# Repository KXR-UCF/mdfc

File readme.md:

## **LTI Modular DAQ & Flight Computer**

This is a teensy 4.1 based analog data acquisition system and flight computer.

It consists of 5 PCBs:

**Heisenberg (Mainboard)**

The Heisenberg board carries the Teensy 4.1 and all the modules, mounts to the chassis, and has the servo/aux connector. It provides the same pinout to each of the two modules so they are interchangeable.

**Fring/Schrader (Flight/Ground Power Modules, these will most likely be two different PCBs)**

These boards convert input voltage, either from battery during flight use or power over ethernet for ground use, into the necessary voltages for the rest of the system. They also handle the ethernet input to the Teensy 4.1, and allow the Teensy 4.1 to independently enable/disable each voltage output.

**Goodman (ADC Module)**
This board carries the HiLetgo ADS1256 board, along with analog circuitry and a sensor connector, for use with analog sensors such as Pressure Transducers, Thermocouples, and Load Cells. A future development will be to create a fully SRAD ADC module instead of relying on the COTS ADS1256 board.

**Pinkman (Flight Sensor/Telemetry Module)**
This board contains flight sensors (IMU and barometric), a GPS receiver, and a 433 MHz LoRa radio for telemetry in flight.

The Heisenberg board has 2 module slots and 1 power module slot, and its two primary configurations are as follows:

* DAQ/Ground use: 
	Module A: Goodman
	Module B: Goodman
	Power Module: Schrader
PoE powered, 16 channel analog input, no flight sensor/telemetry, no servo output.
* Flight use:
	Module A: Goodman
	Module B: Pinkman
	Power Module: Fring
Battery powered, 8 channel analog input, flight sensors/telemetry, servo output.

**The primary goals of this project are:**

* Emulate the EE design, collaboration, integration, and test processes used in the aerospace industry to provide a valuable learning experience for members
* Increase the sampling speed of the DAQ system
* Increase the expandability of the DAQ system
* Move ADCs closer to sensors to decrease analog wire length for less noise
* Improve power filtering for ADCs and load cells
* Record fast analog data in flight
* Transmit flight data to ground via telemetry at the highest speed possible
* Create a platform that can be expanded and upgraded by future students

## Copyright

Copyright © 2026 Knights Experimental Rocketry (KXR). All Rights Reserved.

No permission is granted to reproduce, modify, distribute, manufacture from,
or commercially use the contents of this repository without written
authorization from KXR.

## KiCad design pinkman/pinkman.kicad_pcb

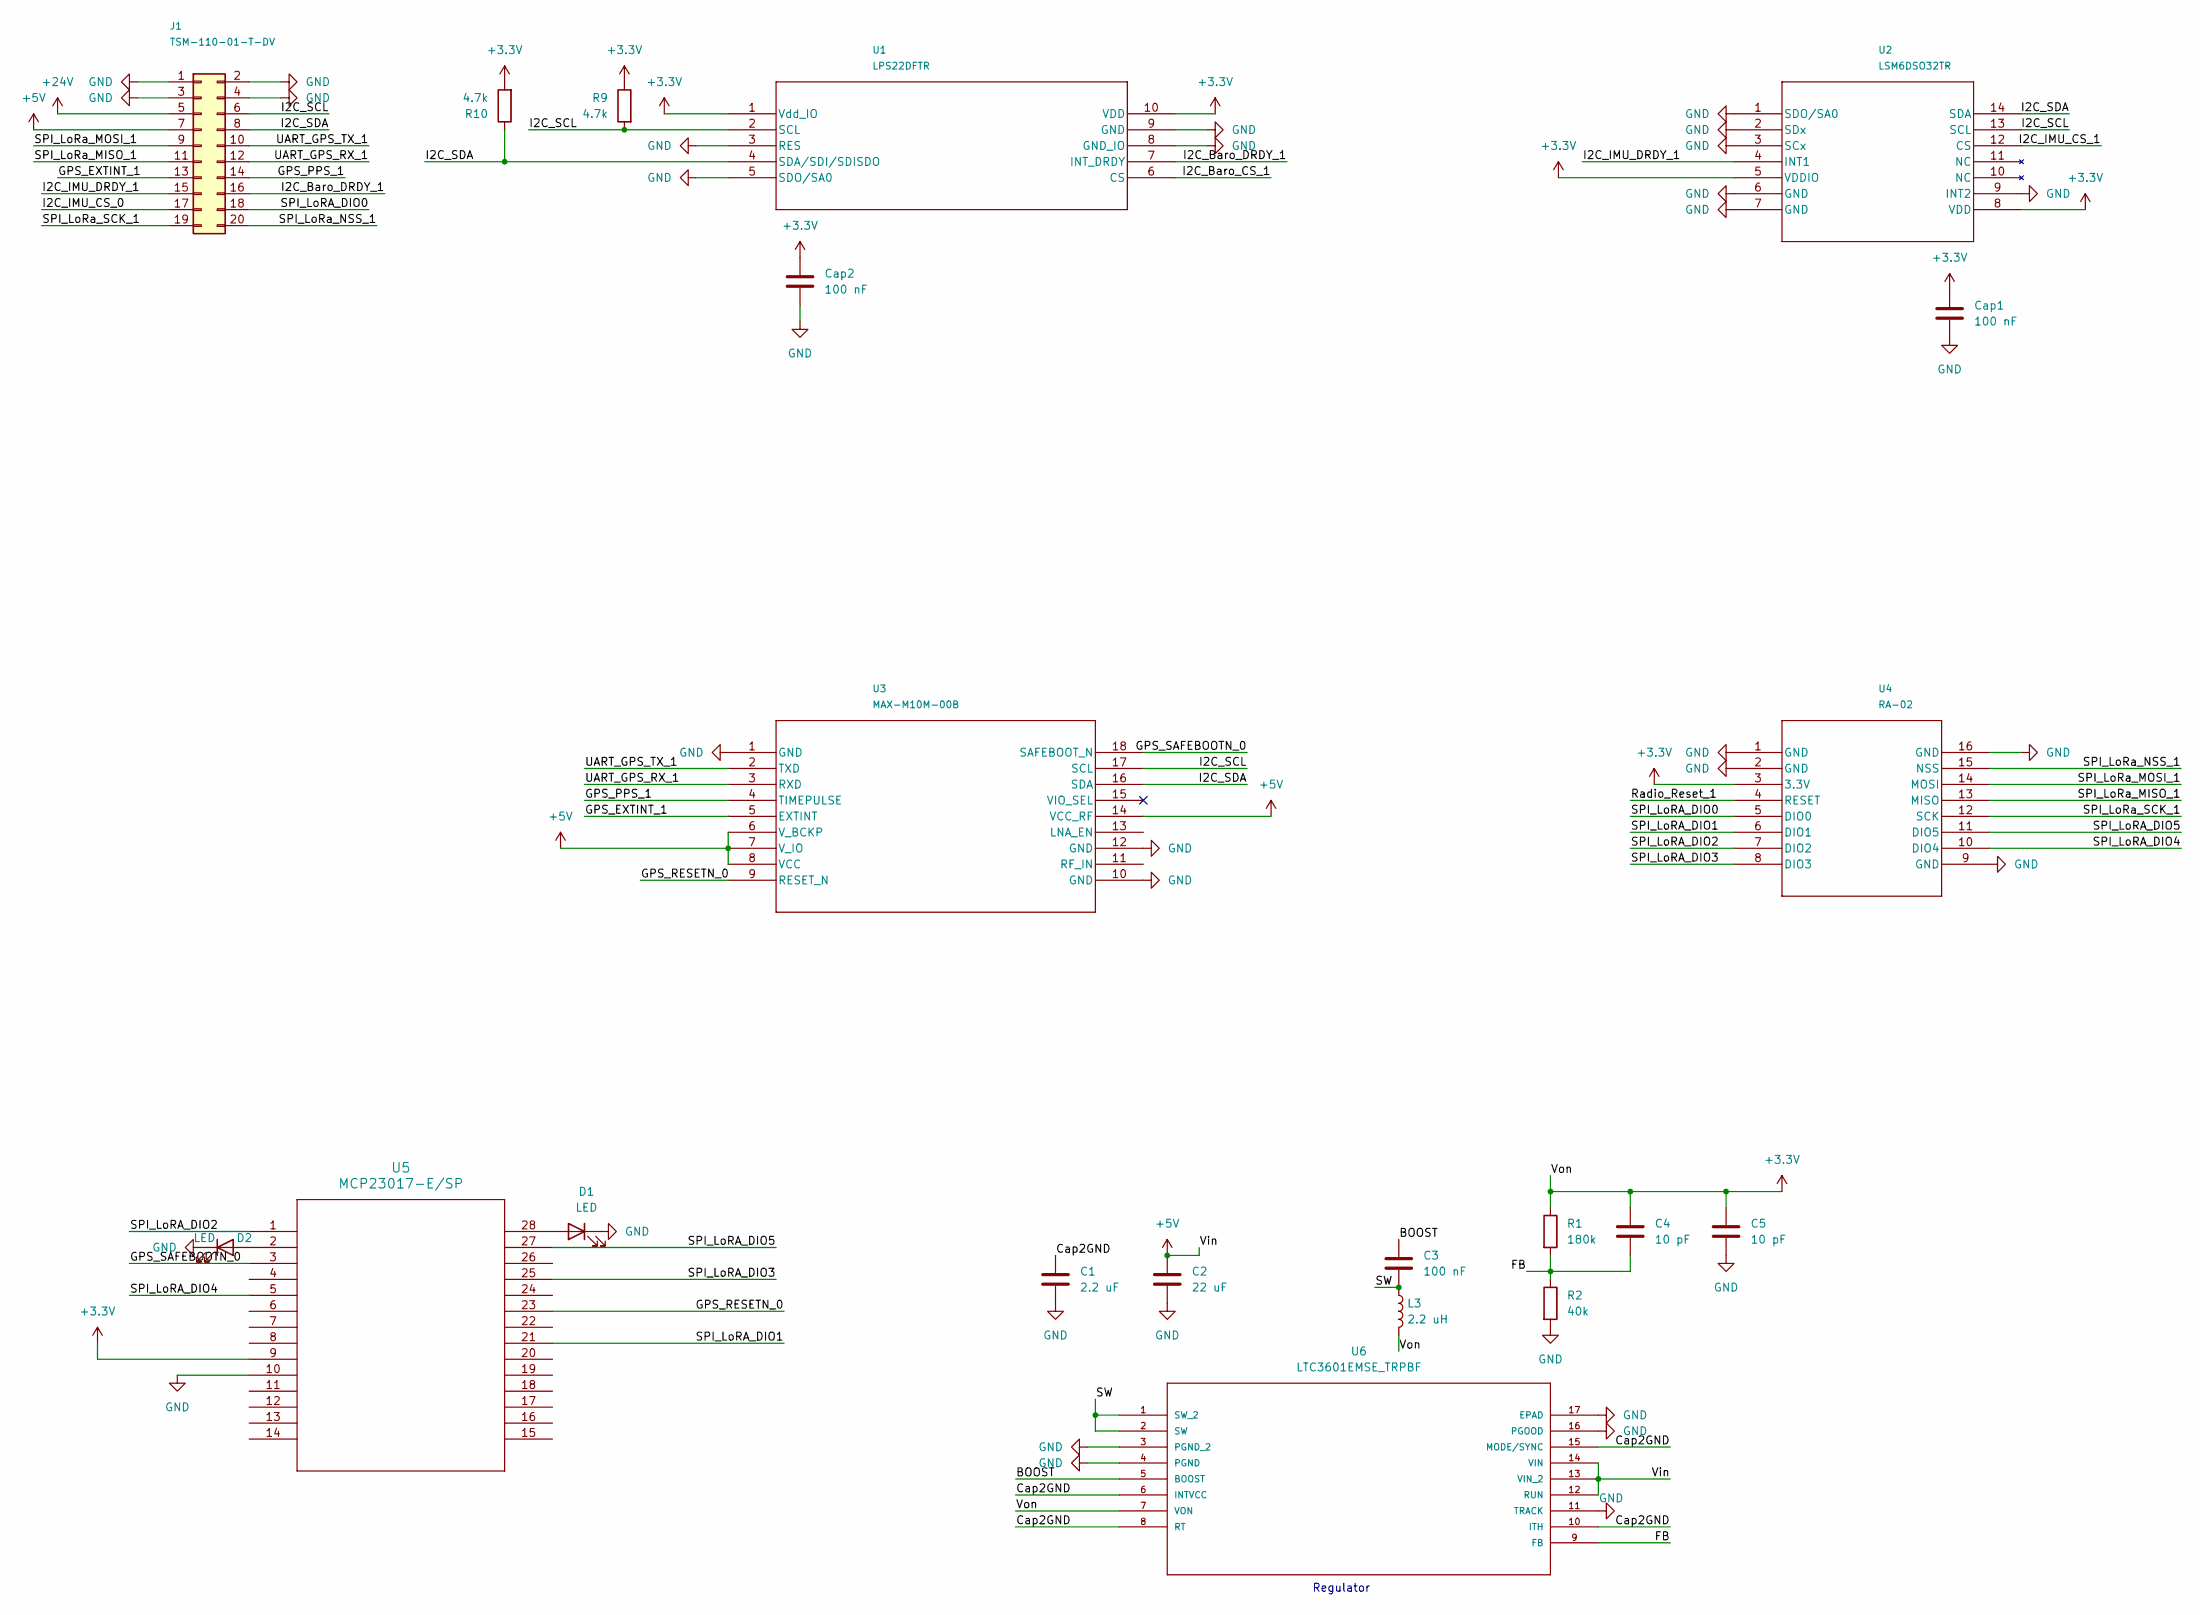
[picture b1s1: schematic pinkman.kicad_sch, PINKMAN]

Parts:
C1: 2.2 uF; C_01005_0402Metric
C2: 22 uF; C_01005_0402Metric
C3: 100 nF; C_01005_0402Metric
C4, C5: 10 pF; C_01005_0402Metric
Cap1, Cap2: 100 nF; TDSON-8-1
D1, D2: LED; LED_01005_0402Metric
J1: TSM-110-01-T-DV; CONN_TSM-110-01-T-DV_SAI
L3: 2.2 uH; VSON-10-1EP_3x3mm_P0.5mm_EP1.65x2.4mm
R1: 180k; DIP-8_W7.62mm
R2: 40k; DIP-8_W7.62mm
R9, R10: 4.7k; R_0201_0603Metric
U1: LPS22DFTR; QFN_22DFTR_STM; MPN LPS22DFTR
U2: LSM6DSO32TR; LGA-14L_2P5X3X0P83_STM; MPN LSM6DSO32TR
U3: MAX-M10M-00B; MOD18_MAX-M10M_UBL; MPN MAX-M10M-00B-01
U4: RA-02; RA-02_AIT; MPN RA-02
U5: MCP23017-E/SP; SPDIP28_300MC_MCH
U6: LTC3601EMSE_TRPBF; MSOP-16_MSE_LIT; MPN LTC3601EMSE#TRPBF; DigiKey_Part_Number LTC3601EMSE#TRPBFCT-ND

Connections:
+3.3V: C4.1, C5.1, Cap1.1, Cap2.1, L3.2, R1.1, R9.1, R10.2, U1.1 (Vdd_IO), U1.10 (VDD), U2.5 (VDDIO), U2.8 (VDD), U4.3 (3.3V), U5.9, U6.7 (VON)
+5V: C2.1, J1.7, U3.6 (V_BCKP), U3.7 (V_IO), U3.8 (VCC), U3.14 (VCC_RF), U6.12 (RUN), U6.13 (VIN_2), U6.14 (VIN)
+24V: J1.5
/BOOST: C3.1, U6.5 (BOOST)
/Cap2GND: C1.1, U6.6 (INTVCC), U6.8 (RT), U6.10 (ITH), U6.15 (MODE/SYNC)
/FB: C4.2, R1.2, R2.1, U6.9 (FB)
/GPS_EXTINT_1: J1.13, U3.5 (EXTINT)
/GPS_PPS_1: J1.14, U3.4 (TIMEPULSE)
/GPS_RESETN_0: U3.9 (RESET_N), U5.23
/GPS_SAFEBOOTN_0: U3.18 (SAFEBOOT_N), U5.3
/I2C_Baro_CS_1: U1.6 (CS)
/I2C_Baro_DRDY_1: J1.16, U1.7 (INT_DRDY)
/I2C_IMU_CS_0: J1.17
/I2C_IMU_CS_1: U2.12 (CS)
/I2C_IMU_DRDY_1: J1.15, U2.4 (INT1)
/I2C_SCL: J1.6, R9.2, U1.2 (SCL), U2.13 (SCL), U3.17 (SCL)
/I2C_SDA: J1.8, R10.1, U1.4 (SDA/SDI/SDISDO), U2.14 (SDA), U3.16 (SDA)
/Radio_Reset_1: U4.4 (RESET)
/SPI_LoRA_DIO0: J1.18, U4.5 (DIO0)
/SPI_LoRA_DIO1: U4.6 (DIO1), U5.21
/SPI_LoRA_DIO2: U4.7 (DIO2), U5.1
/SPI_LoRA_DIO3: U4.8 (DIO3), U5.25
/SPI_LoRA_DIO4: U4.10 (DIO4), U5.5
/SPI_LoRA_DIO5: U4.11 (DIO5), U5.27
/SPI_LoRa_MISO_1: J1.11, U4.13 (MISO)
/SPI_LoRa_MOSI_1: J1.9, U4.14 (MOSI)
/SPI_LoRa_NSS_1: J1.20, U4.15 (NSS)
/SPI_LoRa_SCK_1: J1.19, U4.12 (SCK)
/SW: C3.2, L3.1, U6.1 (SW_2), U6.2 (SW)
/UART_GPS_RX_1: J1.12, U3.3 (RXD)
/UART_GPS_TX_1: J1.10, U3.2 (TXD)
GND: C1.2, C2.2, C5.2, Cap1.2, Cap2.2, D1.1 (K), D2.1 (K), J1.1, J1.2, J1.3, J1.4, R2.2, U1.3 (RES), U1.5 (SDO/SA0), U1.8 (GND_IO), U1.9 (GND), U2.1 (SDO/SA0), U2.2 (SDx), U2.3 (SCx), U2.6 (GND), U2.7 (GND), U2.9 (INT2), U3.1 (GND), U3.10 (GND), U3.12 (GND), U4.1 (GND), U4.2 (GND), U4.9 (GND), U4.16 (GND), U5.10, U6.3 (PGND_2), U6.4 (PGND), U6.11 (TRACK), U6.16 (PGOOD), U6.17 (EPAD)
unnamed: D1.2 (A), U5.28
unnamed: D2.2 (A), U5.2

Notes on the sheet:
Regulator

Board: 2 copper layers, 21 parts (1 on the bottom side), 27 nets, no tracks yet.

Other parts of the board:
J1#2: TSM-110-01-T-DV; CONN_TSM-110-01-T-DV_SAI

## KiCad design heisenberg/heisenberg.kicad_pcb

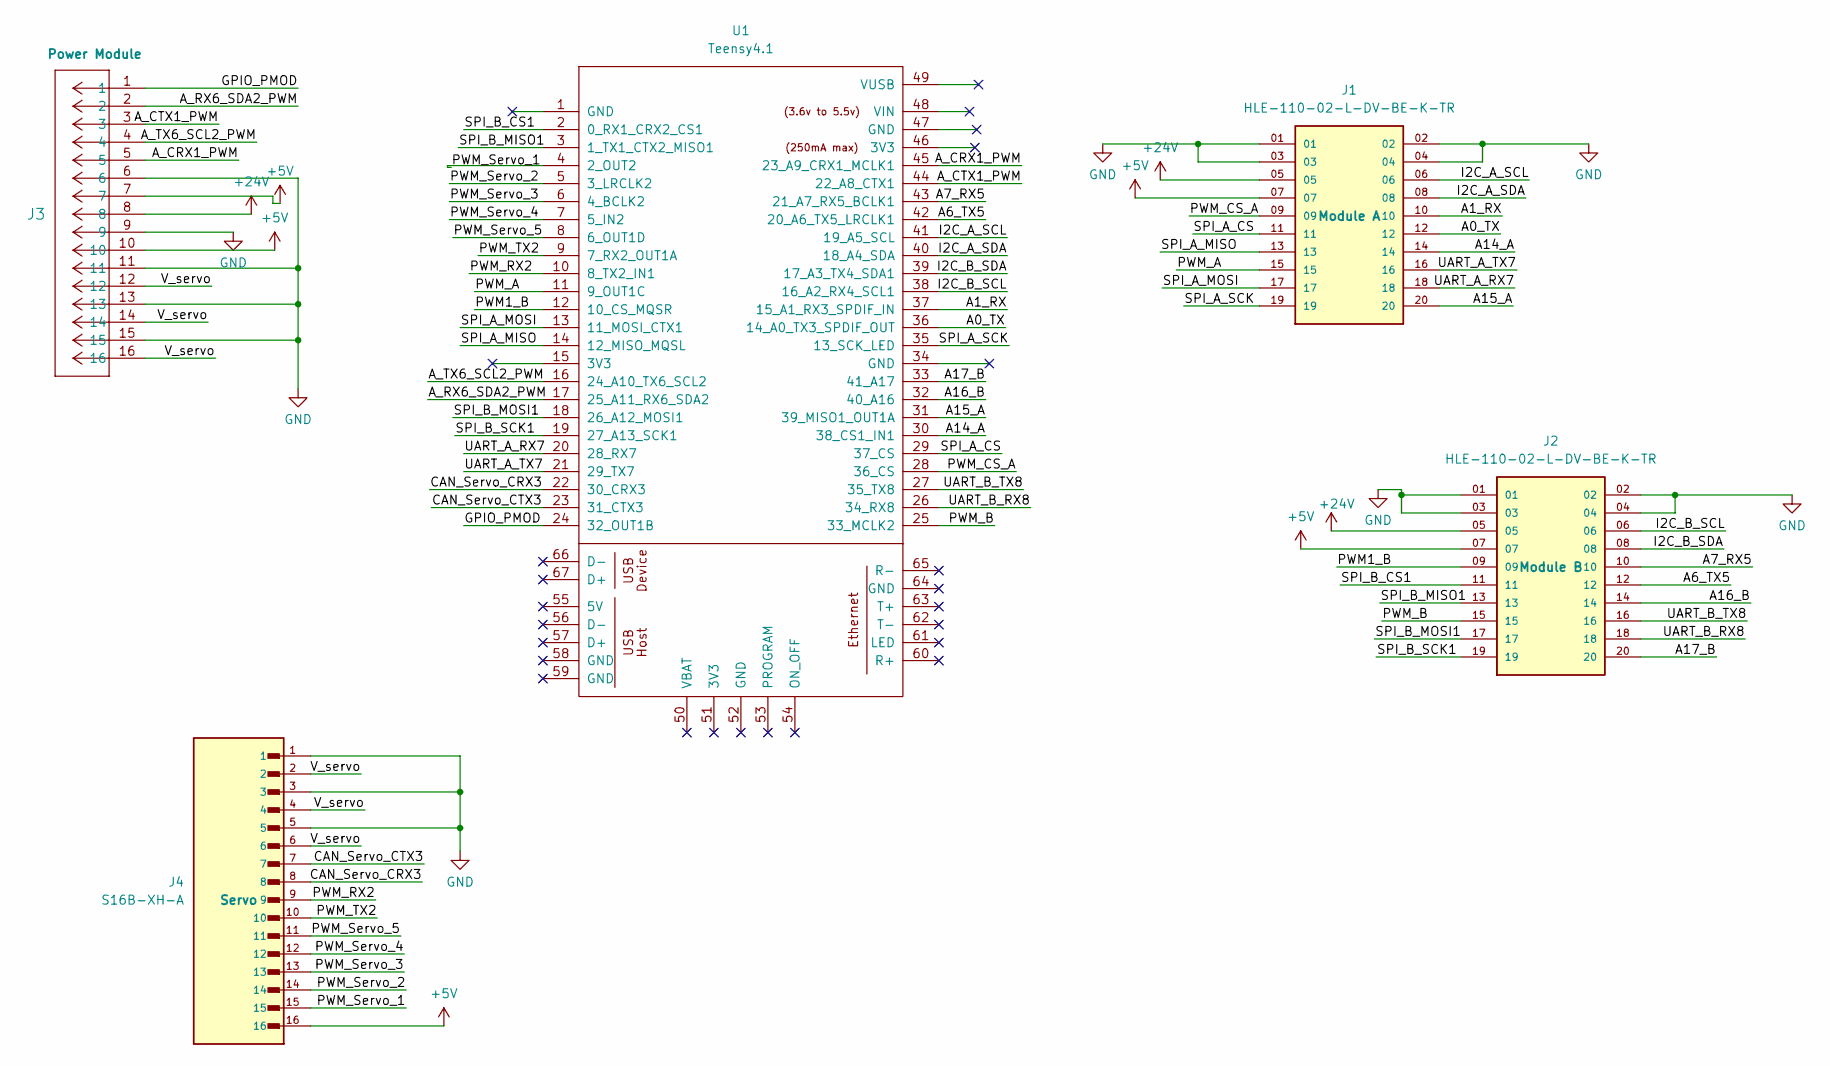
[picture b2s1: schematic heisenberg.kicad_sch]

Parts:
J1, J2: HLE-110-02-L-DV-BE-K-TR; SAMTEC_HLE-110-02-L-DV-BE-K-TR
J3: TSM-108-01-F-DV; CONN_TSM-108-01-F-DV_SAI
J4: S16B-XH-A; JST_XH_S16B-XH-A_1x16_P2.50mm_Horizontal
U1: Teensy4.1; Teensy41

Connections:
+5V: J1.07, J2.07, J3.7, J3.10, J4.16
+24V: J1.05, J2.05, J3.8
/A0_TX: J1.12, U1.36 (14_A0_TX3_SPDIF_OUT)
/A1_RX: J1.10, U1.37 (15_A1_RX3_SPDIF_IN)
/A6_TX5: J2.12, U1.42 (20_A6_TX5_LRCLK1)
/A7_RX5: J2.10, U1.43 (21_A7_RX5_BCLK1)
/A14_A: J1.14, U1.30 (38_CS1_IN1)
/A15_A: J1.20, U1.31 (39_MISO1_OUT1A)
/A16_B: J2.14, U1.32 (40_A16)
/A17_B: J2.20, U1.33 (41_A17)
/A_CRX1_PWM: J3.5, U1.45 (23_A9_CRX1_MCLK1)
/A_CTX1_PWM: J3.3, U1.44 (22_A8_CTX1)
/A_RX6_SDA2_PWM: J3.2, U1.17 (25_A11_RX6_SDA2)
/A_TX6_SCL2_PWM: J3.4, U1.16 (24_A10_TX6_SCL2)
/CAN_Servo_CRX3: J4.8, U1.22 (30_CRX3)
/CAN_Servo_CTX3: J4.7, U1.23 (31_CTX3)
/GPIO_PWR: J3.1, U1.24 (32_OUT1B)
/I2C_A_SCL: J1.06, U1.41 (19_A5_SCL)
/I2C_A_SDA: J1.08, U1.40 (18_A4_SDA)
/I2C_B_SCL: J2.06, U1.38 (16_A2_RX4_SCL1)
/I2C_B_SDA: J2.08, U1.39 (17_A3_TX4_SDA1)
/PWM1_B: J2.09, U1.12 (10_CS_MQSR)
/PWM_1: J4.15, U1.4 (2_OUT2)
/PWM_2: J4.14, U1.5 (3_LRCLK2)
/PWM_3: J4.13, U1.6 (4_BCLK2)
/PWM_4: J4.12, U1.7 (5_IN2)
/PWM_5: J4.11, U1.8 (6_OUT1D)
/PWM_A: J1.15, U1.11 (9_OUT1C)
/PWM_B: J2.15, U1.25 (33_MCLK2)
/PWM_CS_A: J1.09, U1.28 (36_CS)
/PWM_RX2: J4.9, U1.10 (8_TX2_IN1)
/PWM_TX2: J4.10, U1.9 (7_RX2_OUT1A)
/SPI_A_CS: J1.11, U1.29 (37_CS)
/SPI_A_MISO: J1.13, U1.14 (12_MISO_MQSL)
/SPI_A_MOSI: J1.17, U1.13 (11_MOSI_CTX1)
/SPI_A_SCK: J1.19, U1.35 (13_SCK_LED)
/SPI_B_CS1: J2.11, U1.2 (0_RX1_CRX2_CS1)
/SPI_B_MISO1: J2.13, U1.3 (1_TX1_CTX2_MISO1)
/SPI_B_MOSI1: J2.17, U1.18 (26_A12_MOSI1)
/SPI_B_SCK1: J2.19, U1.19 (27_A13_SCK1)
/UART_A_RX7: J1.18, U1.20 (28_RX7)
/UART_A_TX7: J1.16, U1.21 (29_TX7)
/UART_B_RX8: J2.18, U1.26 (34_RX8)
/UART_B_TX8: J2.16, U1.27 (35_TX8)
/V_servo: J3.12, J3.14, J3.16, J4.2, J4.4, J4.6
GND: J1.01, J1.02, J1.03, J1.04, J2.01, J2.02, J2.03, J2.04, J3.6, J3.9, J3.11, J3.13, J3.15, J4.1, J4.3, J4.5

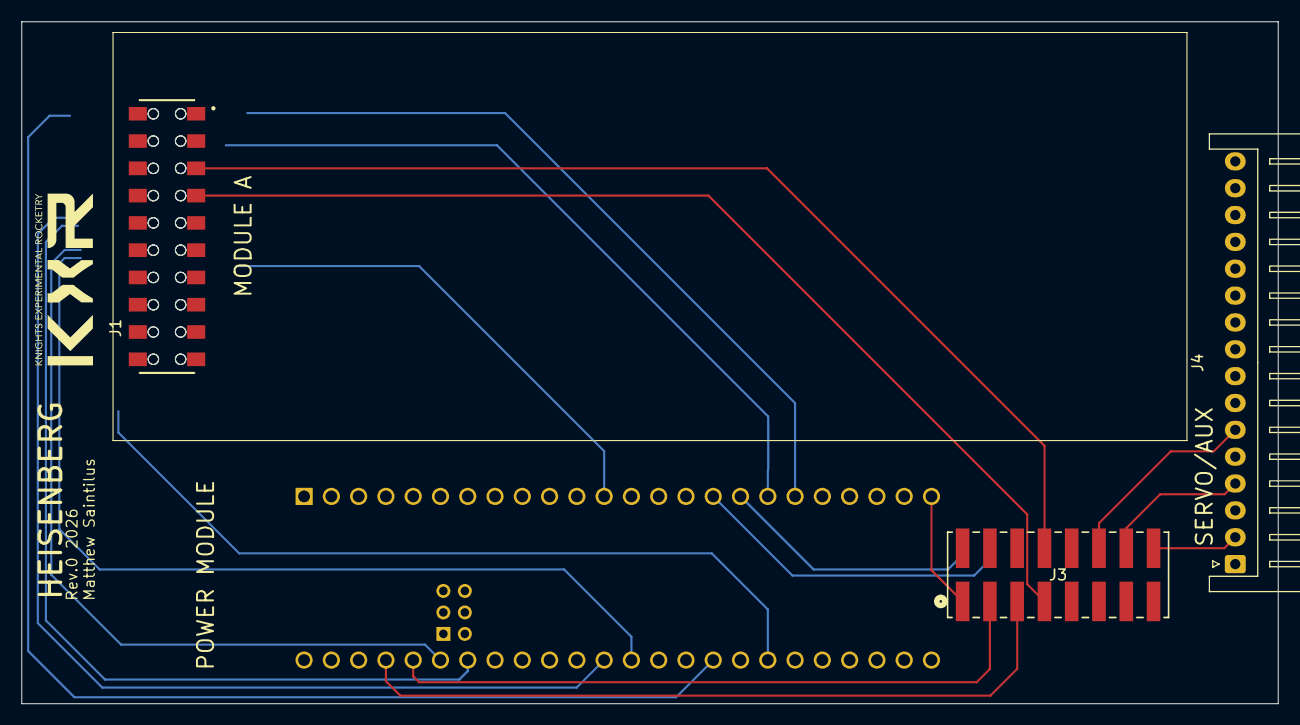
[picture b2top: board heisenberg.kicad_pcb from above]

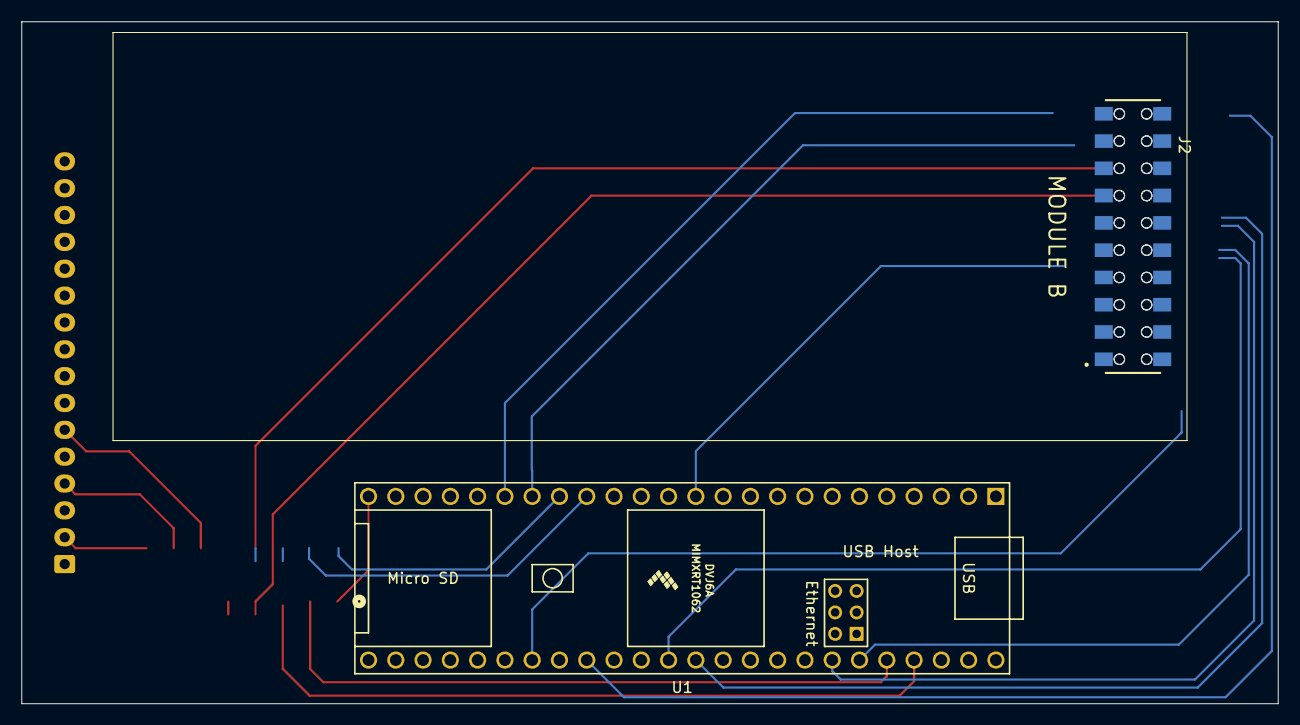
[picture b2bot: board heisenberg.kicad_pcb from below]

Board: 4 copper layers, 117.0 x 63.5 mm, 5 parts (2 on the bottom side), 46 nets.

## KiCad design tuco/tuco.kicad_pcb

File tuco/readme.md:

## TUCO:
Tuco is a large, single sided (except the teensy), 2 layer (ideally) mainboard with test connectors for all the signals coming from the teensy. It acts as an exploded version of Heisenberg, so the software can be bench tested, the power supplies can be stress tested and analyzed, and signal issues can be troubleshooted.

It is designed to fit onto a standard breadboard with the 40 pin header for the module connectors, and the 10 pin header using an extender cable for the servo connector. It has high current screw terminals on the power rails for stress testing the power module, or externally powering the board for testing. It also has larger free space for indicator LEDs or test points to be added at a later date.

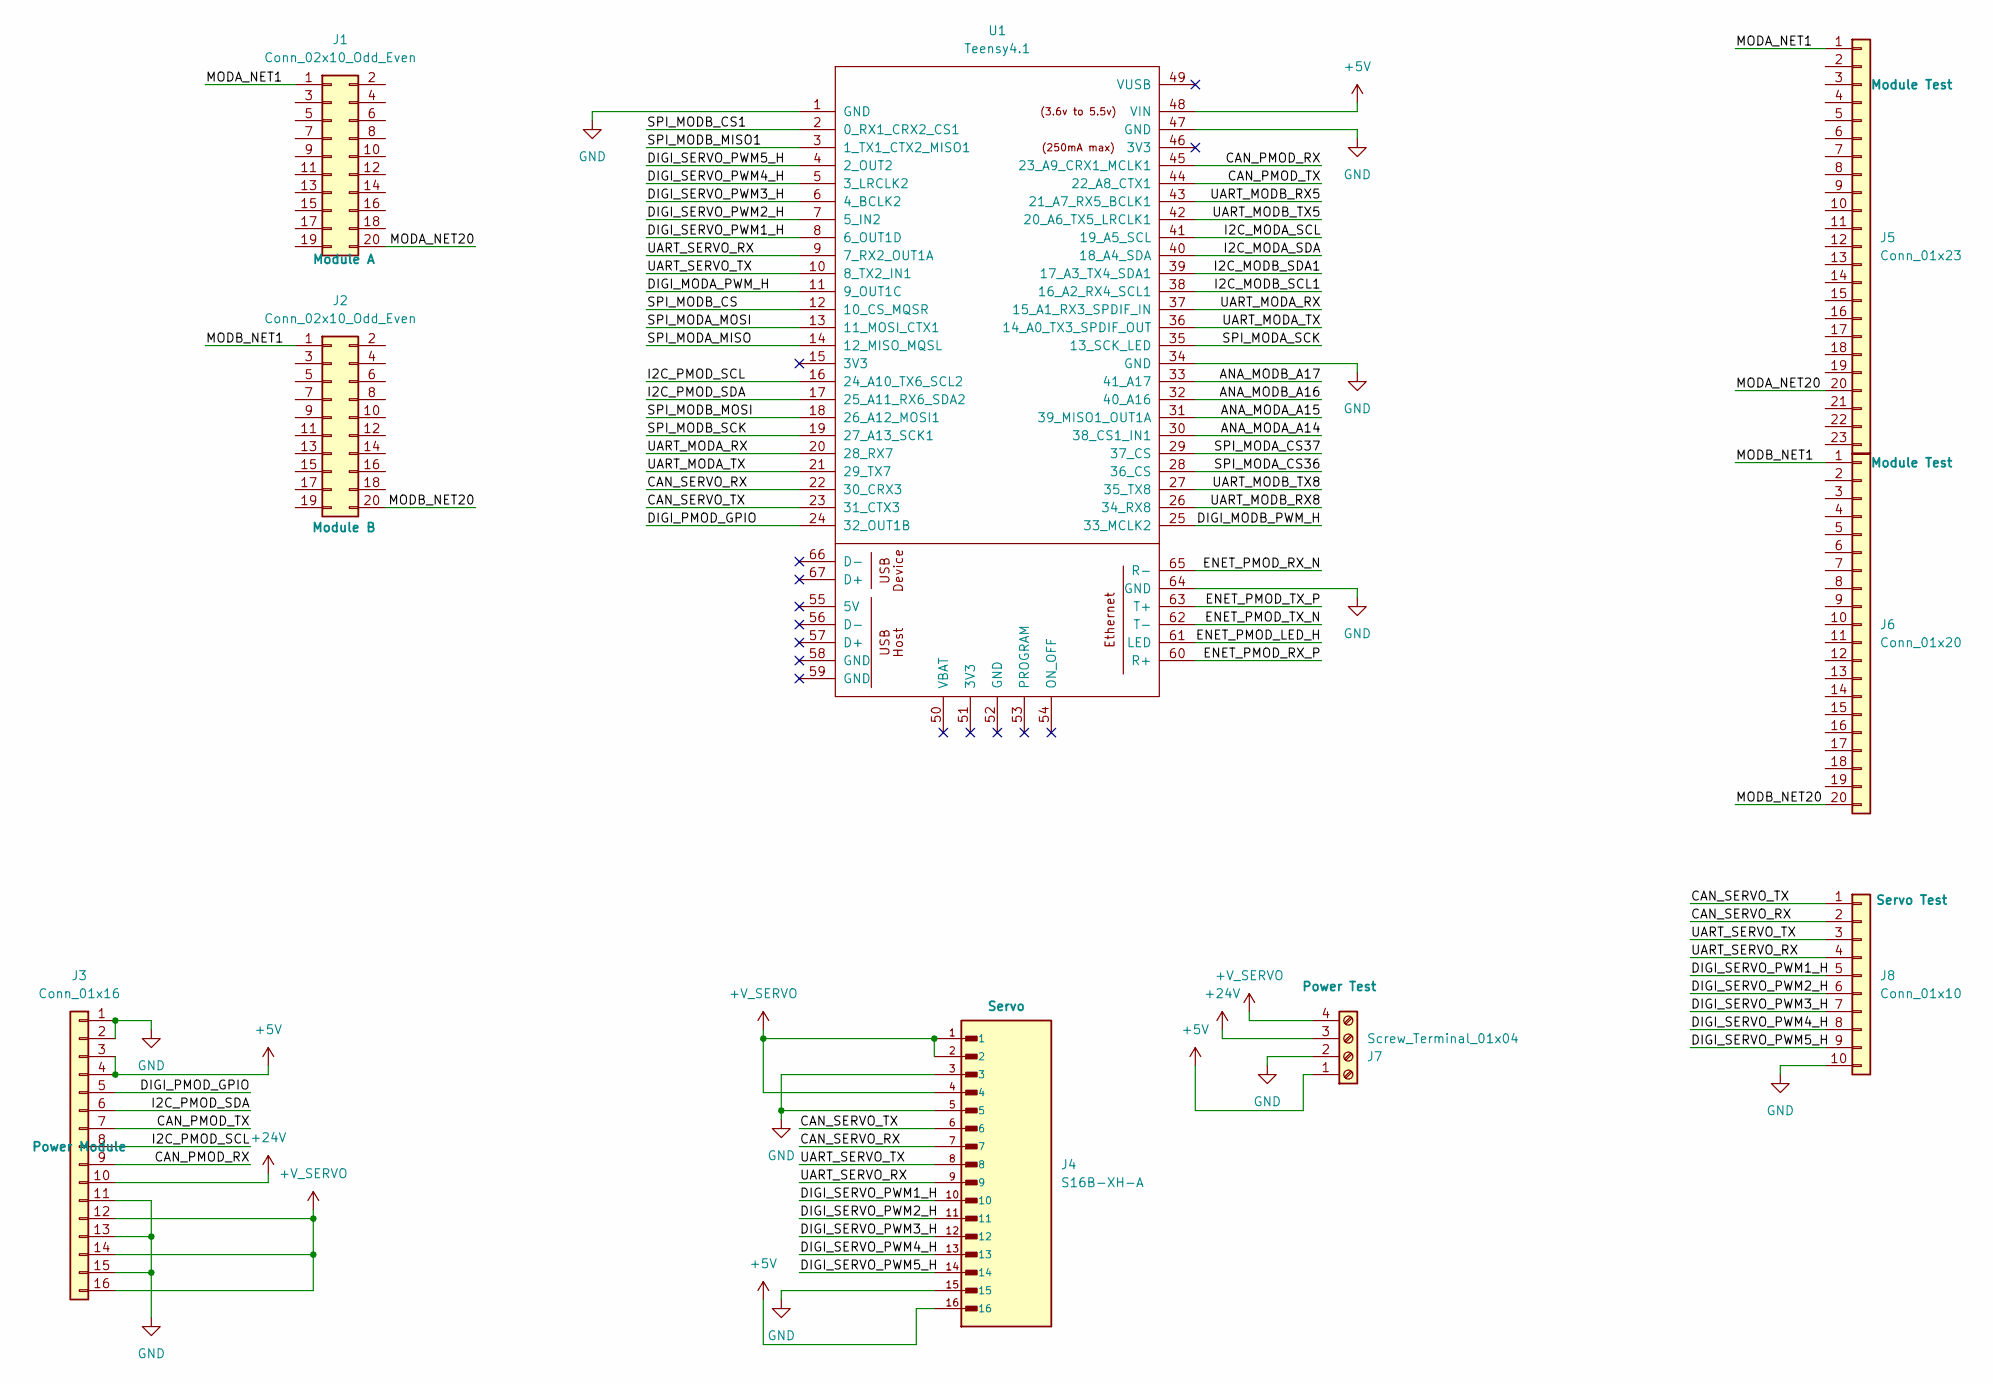
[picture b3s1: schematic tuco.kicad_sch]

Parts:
J1, J2: Conn_02x10_Odd_Even; PinSocket_2x10_P2.54mm_Vertical
J3: Conn_01x16; PinHeader_2x08_P2.54mm_Vertical
J4: S16B-XH-A; JST_XH_S16B-XH-A_1x16_P2.50mm_Horizontal
J5: Conn_01x23; PinHeader_1x23_P2.54mm_Vertical
J6: Conn_01x20; PinHeader_1x20_P2.54mm_Vertical
J7: Screw_Terminal_01x04; TerminalBlock_Phoenix_PT-1,5-4-5.0-H_1x04_P5.00mm_Horizontal
J8: Conn_01x10; PinHeader_1x10_P2.54mm_Vertical
U1: Teensy4.1; Teensy41

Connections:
+5V: J3.3, J3.4, J4.16, J7.1, U1.48 (VIN)
+24V: J3.10, J7.3
+V_SERVO: J3.12, J3.14, J3.16, J4.1, J4.2, J4.4, J7.4
/ANA_MODA_A14: U1.30 (38_CS1_IN1)
/ANA_MODA_A15: U1.31 (39_MISO1_OUT1A)
/ANA_MODB_A16: U1.32 (40_A16)
/ANA_MODB_A17: U1.33 (41_A17)
/CAN_PMOD_RX: J3.9, U1.45 (23_A9_CRX1_MCLK1)
/CAN_PMOD_TX: J3.7, U1.44 (22_A8_CTX1)
/CAN_SERVO_RX: J4.7, J8.2, U1.22 (30_CRX3)
/CAN_SERVO_TX: J4.6, J8.1, U1.23 (31_CTX3)
/DIGI_MODA_PWM_H: U1.11 (9_OUT1C)
/DIGI_MODB_PWM_H: U1.25 (33_MCLK2)
/DIGI_PMOD_GPIO: J3.5, U1.24 (32_OUT1B)
/DIGI_SERVO_PWM1_H: J4.10, J8.5, U1.8 (6_OUT1D)
/DIGI_SERVO_PWM2_H: J4.11, J8.6, U1.7 (5_IN2)
/DIGI_SERVO_PWM3_H: J4.12, J8.7, U1.6 (4_BCLK2)
/DIGI_SERVO_PWM4_H: J4.13, J8.8, U1.5 (3_LRCLK2)
/DIGI_SERVO_PWM5_H: J4.14, J8.9, U1.4 (2_OUT2)
/ENET_PMOD_LED_H: U1.61 (LED)
/ENET_PMOD_RX_N: U1.65 (R-)
/ENET_PMOD_RX_P: U1.60 (R+)
/ENET_PMOD_TX_N: U1.62 (T-)
/ENET_PMOD_TX_P: U1.63 (T+)
/I2C_MODA_SCL: U1.41 (19_A5_SCL)
/I2C_MODA_SDA: U1.40 (18_A4_SDA)
/I2C_MODB_SCL1: U1.38 (16_A2_RX4_SCL1)
/I2C_MODB_SDA1: U1.39 (17_A3_TX4_SDA1)
/I2C_PMOD_SCL: J3.8, U1.16 (24_A10_TX6_SCL2)
/I2C_PMOD_SDA: J3.6, U1.17 (25_A11_RX6_SDA2)
/MODA_NET1: J1.1, J5.1
/MODA_NET20: J1.20, J5.20
/MODB_NET1: J2.1, J6.1
/MODB_NET20: J2.20, J6.20
/SPI_MODA_CS36: U1.28 (36_CS)
/SPI_MODA_CS37: U1.29 (37_CS)
/SPI_MODA_MISO: U1.14 (12_MISO_MQSL)
/SPI_MODA_MOSI: U1.13 (11_MOSI_CTX1)
/SPI_MODA_SCK: U1.35 (13_SCK_LED)
/SPI_MODB_CS: U1.12 (10_CS_MQSR)
/SPI_MODB_CS1: U1.2 (0_RX1_CRX2_CS1)
/SPI_MODB_MISO1: U1.3 (1_TX1_CTX2_MISO1)
/SPI_MODB_MOSI: U1.18 (26_A12_MOSI1)
/SPI_MODB_SCK: U1.19 (27_A13_SCK1)
/UART_MODA_RX: U1.20 (28_RX7), U1.37 (15_A1_RX3_SPDIF_IN)
/UART_MODA_TX: U1.21 (29_TX7), U1.36 (14_A0_TX3_SPDIF_OUT)
/UART_MODB_RX5: U1.43 (21_A7_RX5_BCLK1)
/UART_MODB_RX8: U1.26 (34_RX8)
/UART_MODB_TX5: U1.42 (20_A6_TX5_LRCLK1)
/UART_MODB_TX8: U1.27 (35_TX8)
/UART_SERVO_RX: J4.9, J8.4, U1.9 (7_RX2_OUT1A)
/UART_SERVO_TX: J4.8, J8.3, U1.10 (8_TX2_IN1)
GND: J3.1, J3.2, J3.11, J3.13, J3.15, J4.3, J4.5, J4.15, J7.2, J8.10, U1.1 (GND), U1.34 (GND), U1.47 (GND), U1.64 (GND)

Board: 2 copper layers, 9 parts (1 on the bottom side), 24 nets, no tracks yet.
